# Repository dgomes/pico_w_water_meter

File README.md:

# Water Meter Sensor

Monitor your water usage through an energy-efficient IoT device attached to your water provider meter (which happens to have a metal "butterfly wheel) like the JANZ JT400:

This project enables you to monitor the water usage of your household water usage through the use of a DIY water meter sensor built using:

- [Raspberry Pi Pico W](https://www.raspberrypi.com/documentation/microcontrollers/raspberry-pi-pico.html)
- [Inductive Proximity Sensor Detection Switch - TL-W5MC1](https://www.aliexpress.com/item/32973109912.html)
- [TI High-Speed CMOS Logic 14-Stage Binary Counter](https://www.ti.com/lit/ds/symlink/cd54hc4020.pdf)

The RPI Pico W is very flexible in terms of power requirements, but in my case, I use:

- 18650 Battery
- [18650 TP4056 Lithium Battery Charger Module With Protection](https://www.aliexpress.com/item/32930640893.html)
- [Mini Boost Module Step Up Board 5V](https://www.aliexpress.com/item/4000626913742.html) (to power the Inductive Proximity Sensor which states minimum 6V but actually works with 5V)

Just assemble everything :)

You can find the PCB source files (KiCAD) in the respective directory. ([PCB files](https://github.com/dgomes/pico_w_water_meter/tree/main/Water%20Meter%20PCB))

I designed a 3D-printed adapter for the Inductive Proximity Sensor to fit the JANZ JT400.  ([3Dadapter](https://github.com/dgomes/pico_w_water_meter/tree/main/3Dadapter))

The RPi Pico W is flashed with a micropython firmware and then you upload the project available in `src`

You must have an MQTT broker (e.g. Mosquitto)

The project automatically integrates with [Home Assistant](https://www.home-assistant.io)

# config.py

You will need to create an additional file called `config.py` that must include the variables:

```python
SSID = "myhome_network"
WIFI_PASSWORD = "blablabla" 

SERVER = "192.168.1.1"  #this is your MQTT Broker Address
USER = None #change this to your MQTT username, else leave None
PASSWORD = None #change this to your MQTT password, else leave None

```

# Powering

- Using a 18650 3.7v battery the sensor can run for 2 weeks
- Using a battery pack of 4 AA batteries the sensor can run for 4 weeks

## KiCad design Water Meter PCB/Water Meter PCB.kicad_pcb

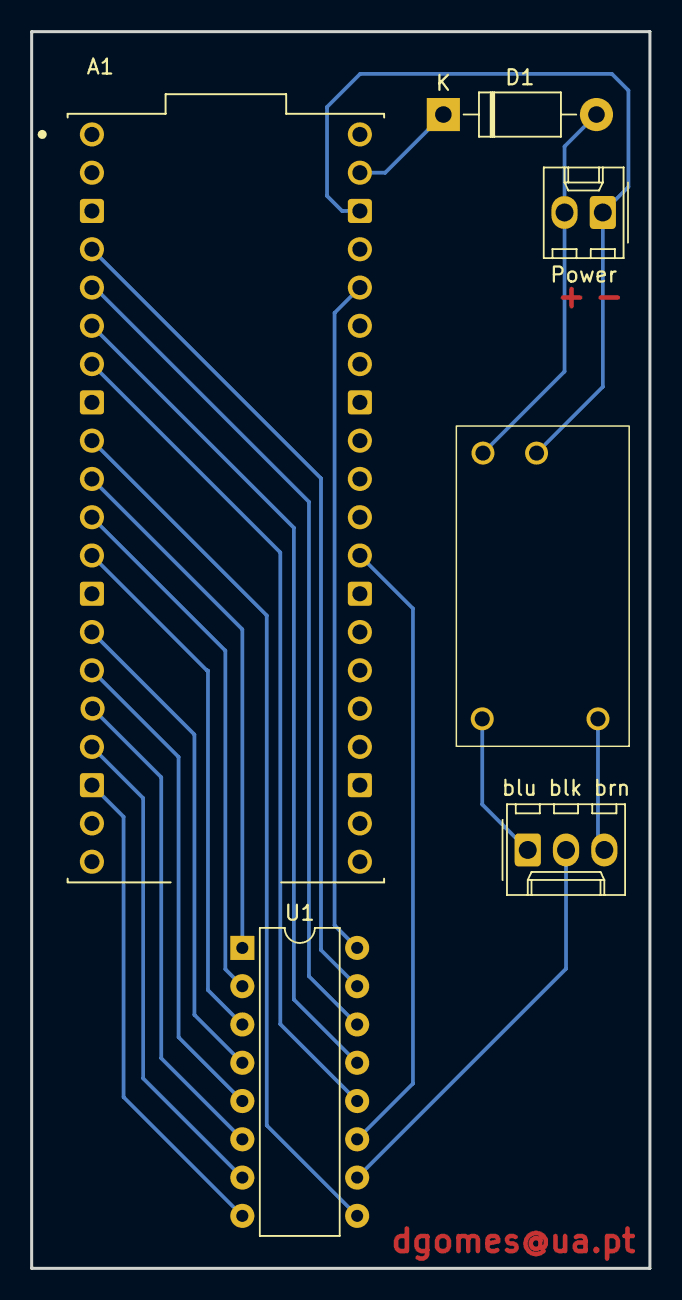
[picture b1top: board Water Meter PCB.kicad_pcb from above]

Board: 2 copper layers, 41.0 x 82.1 mm, 6 parts (0 on the bottom side), 21 nets.

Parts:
A1: SC0918; MODULE_SC0918
BS01+1: BS01+
D1: 1N5819; D_DO-41_SOD81_P10.16mm_Horizontal
Power: pos; Molex_KK-254_AE-6410-02A_1x02_P2.54mm_Vertical
U1: 4020; DIP-16_W7.62mm
blu blk brn: TL-W5MC1; Molex_KK-254_AE-6410-03A_1x03_P2.54mm_Vertical

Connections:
unnamed: A1.36 (3V3_OUT), U1.16 (VDD)
unnamed: A1.4 (GP2), U1.15 (Q10)
unnamed: A1.5 (GP3), U1.14 (Q9)
unnamed: A1.6 (GP4), U1.13 (Q7)
unnamed: A1.7 (GP5), U1.12 (Q8)
unnamed: A1.9 (GP6), U1.9 (Q0)
unnamed: A1.10 (GP7), U1.1 (Q11)
unnamed: A1.11 (GP8), U1.2 (Q12)
unnamed: A1.12 (GP9), U1.3 (Q13)
unnamed: A1.14 (GP10), U1.4 (Q5)
unnamed: A1.15 (GP11), U1.5 (Q4)
unnamed: A1.16 (GP12), U1.6 (Q6)
unnamed: A1.17 (GP13), U1.7 (Q3)
unnamed: A1.29 (GP22), U1.11 (Reset)
unnamed: A1.39 (VSYS), D1.1 (K)
unnamed: BS01+1.4 (in_+), D1.2 (A), Power.2
unnamed: A1.38 (GND), BS01+1.3 (in_-), Power.1
unnamed: BS01+1.1 (out_+), blu blk brn.3
unnamed: BS01+1.2 (out_-), blu blk brn.1
unnamed: U1.10 (CLK), blu blk brn.2
unnamed: A1.18 (GND), U1.8 (VSS)

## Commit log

2023-02-24 Initial Version
2023-03-11 current deployed version
2023-03-11 add media
2023-03-11 improve description
2023-03-11 spellcheck
2023-03-11 more info
2023-03-16 typo
2023-04-05 Add MQTT username/password
2023-05-17 fix m3 conversion
2023-06-08 fix unit
2023-09-02 fix mqtt
